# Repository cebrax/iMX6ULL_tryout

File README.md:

# iMX6ULL_tryout

This is a test board to get iMX6ULL up and running using KiCad 5.99

The board has:

- iMX6ULL 900MHz MCIMX6Y2DVM09AB
- 512MB DDR3L RAM
- An SD card slot
- 2 x USB connector
- An ethernet PHY and connector with magnetics
- A 40-pin LCD connector
- Various pinouts of GPIO, RS232 and such..

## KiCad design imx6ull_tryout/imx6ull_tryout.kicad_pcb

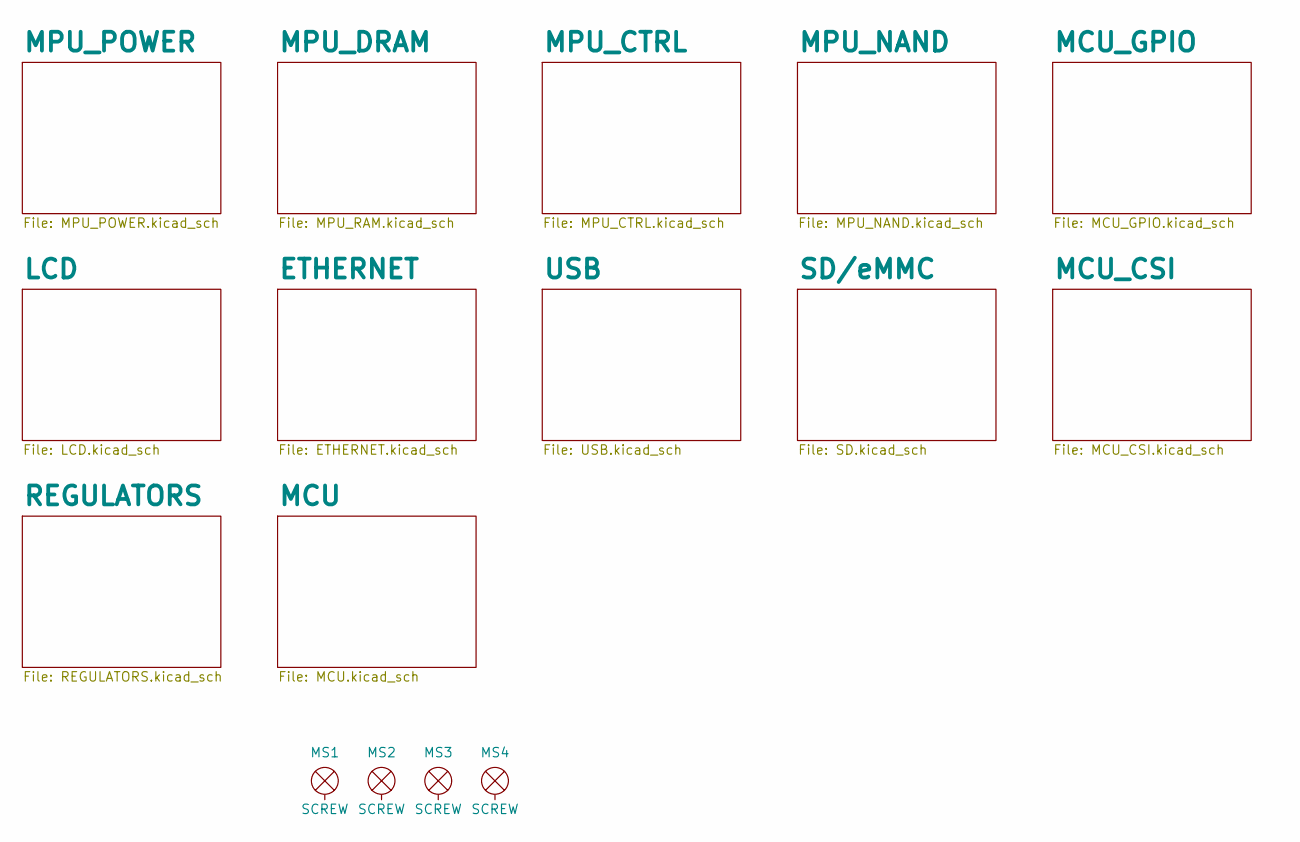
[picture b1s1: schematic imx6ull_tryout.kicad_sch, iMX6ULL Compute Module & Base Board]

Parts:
MS1, MS2, MS3, MS4: SCREW; M3-Screw-Front

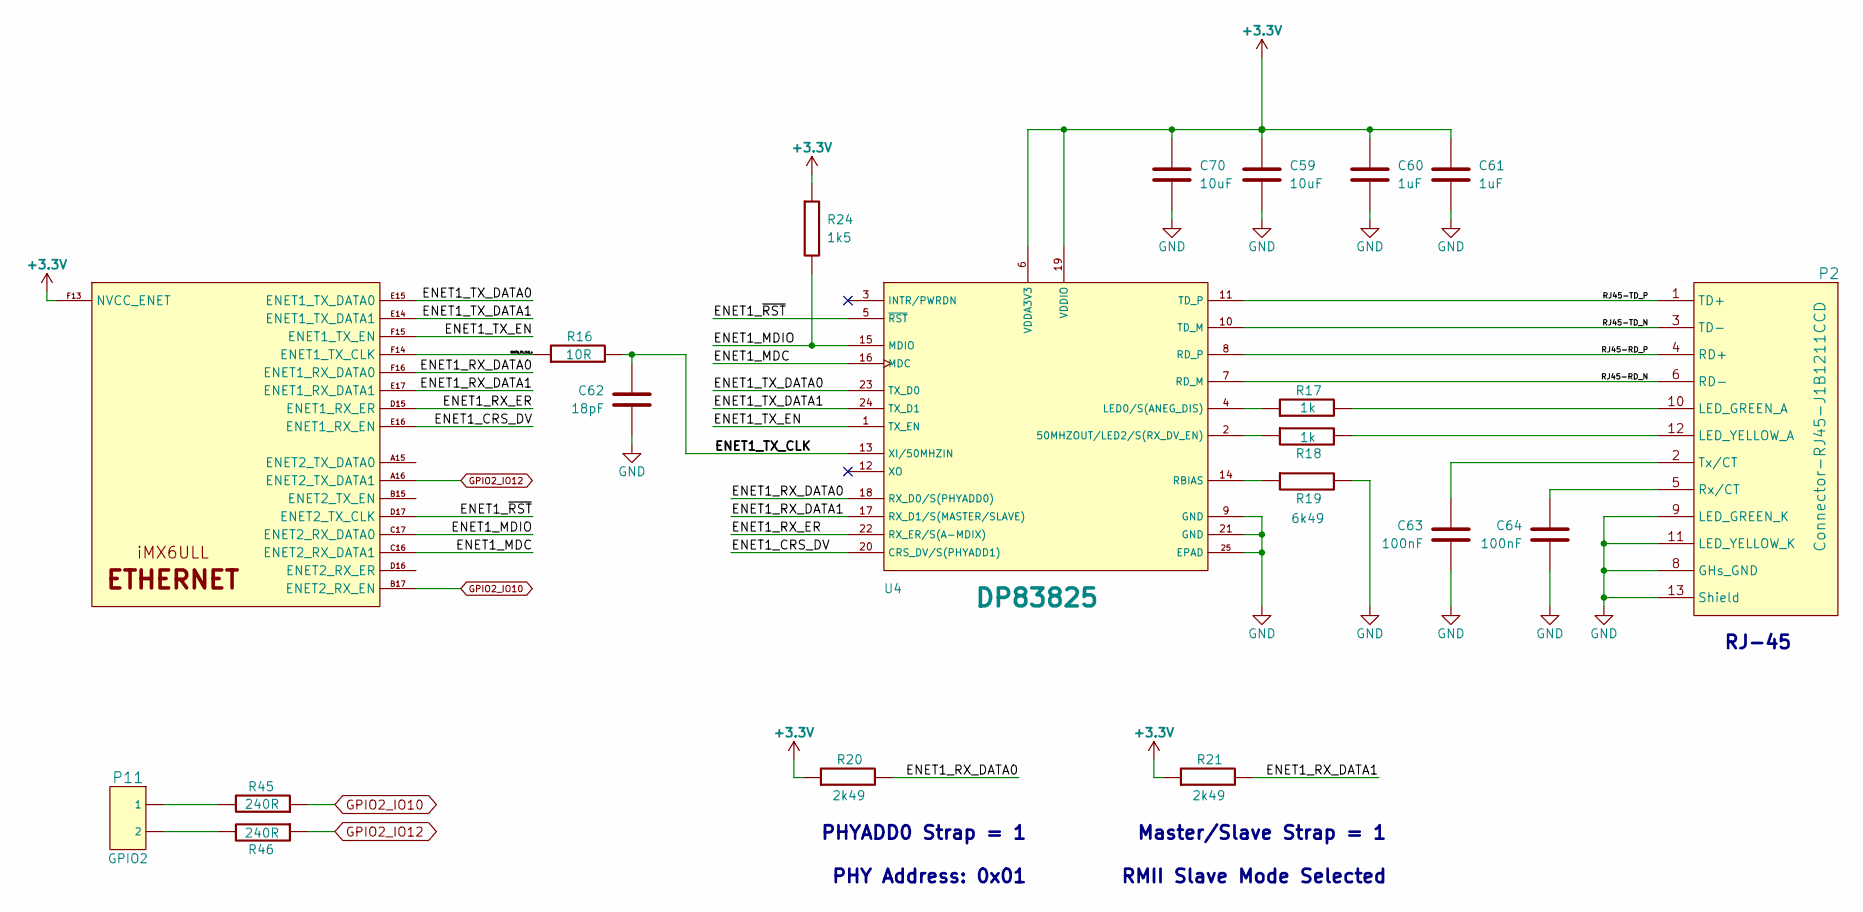
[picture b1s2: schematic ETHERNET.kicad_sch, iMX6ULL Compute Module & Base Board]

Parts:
C59, C70: 10uF; IPC-SMD-C-0402; Voltage 16V
C60, C61: 1uF; IPC-SMD-C-0402; Voltage 10V
C62: 18pF; IPC-SMD-C-0402; Voltage 50V
C63, C64: 100nF; IPC-SMD-C-0805; Voltage 50V
P2: Connector-RJ45-J1B1211CCD
P11: GPIO2; Connector-Male-Breakaway-2pins
R16: 10R; IPC-SMD-R-0402
R17, R18: 1k; IPC-SMD-R-0805
R19: 6k49; IPC-SMD-R-0603
R20, R21: 2k49; IPC-SMD-R-0603
R24: 1k5; IPC-SMD-R-0603
R45, R46: 240R; IPC-SMD-R-0402
U1: iMX6ULL; BGA289C80P17X17_1400X1400X132N
U4: DP83825; IPC-WQFN-24

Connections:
+3V3: C59.1, C60.1, C61.1, C70.1, R20.1, R21.1, R24.1, U1.F13 (NVCC_ENET), U4.6 (VDDA3V3), U4.19 (VDDIO); also elsewhere on the board
/ETHERNET/ENET1_CRS_DV: U1.E16 (ENET1_RX_EN), U4.20 (CRS_DV/S(PHYADD1))
/ETHERNET/ENET1_MDC: U1.C16 (ENET2_RX_DATA1), U4.16 (MDC)
/ETHERNET/ENET1_MDIO: R24.2, U1.C17 (ENET2_RX_DATA0), U4.15 (MDIO)
/ETHERNET/ENET1_RX_DATA0: R20.2, U1.F16 (ENET1_RX_DATA0), U4.18 (RX_D0/S(PHYADD0))
/ETHERNET/ENET1_RX_DATA1: R21.2, U1.E17 (ENET1_RX_DATA1), U4.17 (RX_D1/S(MASTER/SLAVE))
/ETHERNET/ENET1_RX_ER: U1.D15 (ENET1_RX_ER), U4.22 (RX_ER/S(A-MDIX))
/ETHERNET/ENET1_TX_CLK: C62.1, R16.2, U4.13 (XI/50MHZIN)
/ETHERNET/ENET1_TX_CLK_s: R16.1, U1.F14 (ENET1_TX_CLK)
/ETHERNET/ENET1_TX_DATA0: U1.E15 (ENET1_TX_DATA0), U4.23 (TX_D0)
/ETHERNET/ENET1_TX_DATA1: U1.E14 (ENET1_TX_DATA1), U4.24 (TX_D1)
/ETHERNET/ENET1_TX_EN: U1.F15 (ENET1_TX_EN), U4.1 (TX_EN)
/ETHERNET/ENET1_~RST: U1.D17 (ENET2_TX_CLK), U4.5 (~RST)
/ETHERNET/RJ45-RD_N: P2.6 (RD-), U4.7 (RD_M)
/ETHERNET/RJ45-RD_P: P2.4 (RD+), U4.8 (RD_P)
/ETHERNET/RJ45-TD_N: P2.3 (TD-), U4.10 (TD_M)
/ETHERNET/RJ45-TD_P: P2.1 (TD+), U4.11 (TD_P)
GND: C59.2, C60.2, C61.2, C62.2, C63.2, C64.2, C70.2, P2.8 (GHs_GND), P2.9 (LED_GREEN_K), P2.11 (LED_YELLOW_K), P2.13 (Shield), R19.2, U4.9 (GND), U4.21 (GND), U4.25 (EPAD); also elsewhere on the board
GPIO2_IO10: R45.1, U1.B17 (ENET2_RX_EN)
GPIO2_IO12: R46.1, U1.A16 (ENET2_TX_DATA1)
unnamed: C63.1, P2.2 (Tx/CT)
unnamed: C64.1, P2.5 (Rx/CT)
unnamed: P2.10 (LED_GREEN_A), R17.2
unnamed: P2.12 (LED_YELLOW_A), R18.2
unnamed: P11.1, R45.2
unnamed: P11.2, R46.2
unnamed: R17.1, U4.4 (LED0/S(ANEG_DIS))
unnamed: R18.1, U4.2 (50MHZOUT/LED2/S(RX_DV_EN))
unnamed: R19.1, U4.14 (RBIAS)

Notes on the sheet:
PHYADD0 Strap = 1 PHY Address: 0x01
Master/Slave Strap = 1 RMII Slave Mode Selected
RJ-45

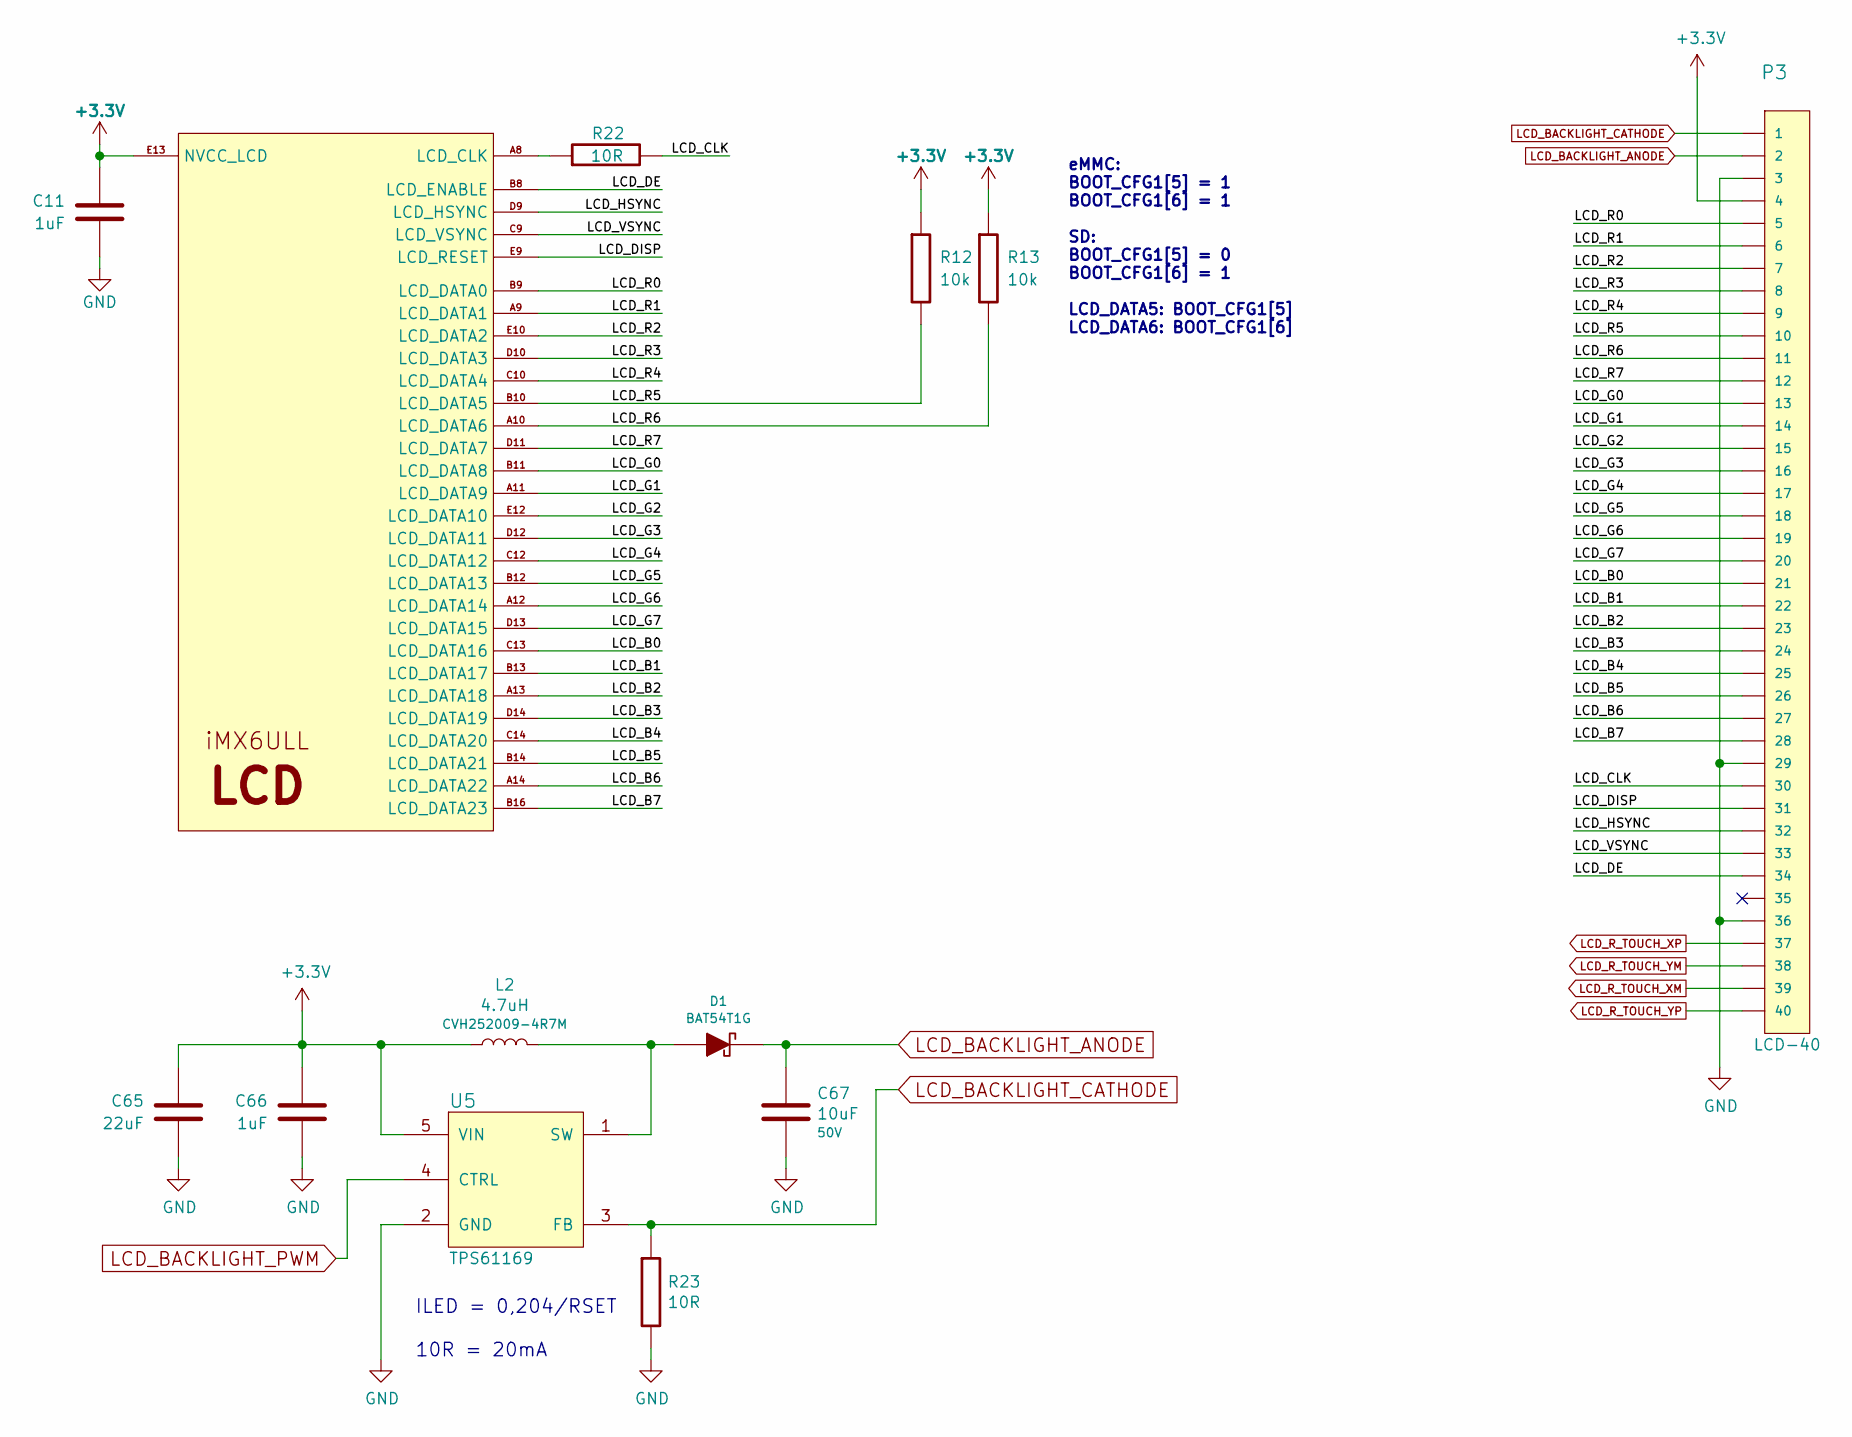
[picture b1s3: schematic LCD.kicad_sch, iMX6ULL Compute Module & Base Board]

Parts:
C11, C66: 1uF; IPC-SMD-C-0402; Voltage 10V
C65: 22uF; IPC-SMD-C-0603; Voltage 6.3V
C67: 10uF; IPC-SMD-C-1206; Voltage 50V
D1: BAT54T1G; IPC-SOD-123
L2: 4.7uH; IPC-SMD-R-0805; Part No CVH252009-4R7M
P3: LCD-40; Connector-SMD-ZIF-40-pin
R12, R13: 10k; IPC-SMD-R-0603
R22: 10R; IPC-SMD-R-0402
R23: 10R; IPC-SMD-R-0805
U1: iMX6ULL; BGA289C80P17X17_1400X1400X132N
U5: TPS61169; IPC-SC-70-5

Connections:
+3V3: C11.1, C65.1, C66.1, L2.2, P3.4, R12.1, R13.1, U1.E13 (NVCC_LCD), U5.5 (VIN); also elsewhere on the board
/LCD/LCD_B0: P3.21, U1.C13 (LCD_DATA16)
/LCD/LCD_B1: P3.22, U1.B13 (LCD_DATA17)
/LCD/LCD_B2: P3.23, U1.A13 (LCD_DATA18)
/LCD/LCD_B3: P3.24, U1.D14 (LCD_DATA19)
/LCD/LCD_B4: P3.25, U1.C14 (LCD_DATA20)
/LCD/LCD_B5: P3.26, U1.B14 (LCD_DATA21)
/LCD/LCD_B6: P3.27, U1.A14 (LCD_DATA22)
/LCD/LCD_B7: P3.28, U1.B16 (LCD_DATA23)
/LCD/LCD_CLK: P3.30, R22.2
/LCD/LCD_DE: P3.34, U1.B8 (LCD_ENABLE)
/LCD/LCD_DISP: P3.31, U1.E9 (LCD_RESET)
/LCD/LCD_G0: P3.13, U1.B11 (LCD_DATA8)
/LCD/LCD_G1: P3.14, U1.A11 (LCD_DATA9)
/LCD/LCD_G2: P3.15, U1.E12 (LCD_DATA10)
/LCD/LCD_G3: P3.16, U1.D12 (LCD_DATA11)
/LCD/LCD_G4: P3.17, U1.C12 (LCD_DATA12)
/LCD/LCD_G5: P3.18, U1.B12 (LCD_DATA13)
/LCD/LCD_G6: P3.19, U1.A12 (LCD_DATA14)
/LCD/LCD_G7: P3.20, U1.D13 (LCD_DATA15)
/LCD/LCD_HSYNC: P3.32, U1.D9 (LCD_HSYNC)
/LCD/LCD_R0: P3.5, U1.B9 (LCD_DATA0)
/LCD/LCD_R1: P3.6, U1.A9 (LCD_DATA1)
/LCD/LCD_R2: P3.7, U1.E10 (LCD_DATA2)
/LCD/LCD_R3: P3.8, U1.D10 (LCD_DATA3)
/LCD/LCD_R4: P3.9, U1.C10 (LCD_DATA4)
/LCD/LCD_R5: P3.10, R12.2, U1.B10 (LCD_DATA5)
/LCD/LCD_R6: P3.11, R13.2, U1.A10 (LCD_DATA6)
/LCD/LCD_R7: P3.12, U1.D11 (LCD_DATA7)
/LCD/LCD_VSYNC: P3.33, U1.C9 (LCD_VSYNC)
GND: C11.2, C65.2, C66.2, C67.2, P3.3, P3.29, P3.36, R23.2, U5.2 (GND); also elsewhere on the board
LCD_BACKLIGHT_ANODE: C67.1, D1.2 (K), P3.2
LCD_BACKLIGHT_CATHODE: P3.1, R23.1, U5.3 (FB)
LCD_BACKLIGHT_PWM: U5.4 (CTRL); also elsewhere on the board
LCD_R_TOUCH_XM: P3.39; also elsewhere on the board
LCD_R_TOUCH_XP: P3.37; also elsewhere on the board
LCD_R_TOUCH_YM: P3.38; also elsewhere on the board
LCD_R_TOUCH_YP: P3.40; also elsewhere on the board
unnamed: D1.1 (A), L2.1, U5.1 (SW)
unnamed: R22.1, U1.A8 (LCD_CLK)

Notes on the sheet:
ILED = 0,204/RSET 10R = 20mA
eMMC: BOOT_CFG1[5] = 1 BOOT_CFG1[6] = 1 SD: BOOT_CFG1[5] = 0 BOOT_CFG1[6] = 1 LCD_DATA5: BOOT_CFG1[5] LCD_DATA6: BOOT_CFG1[6]

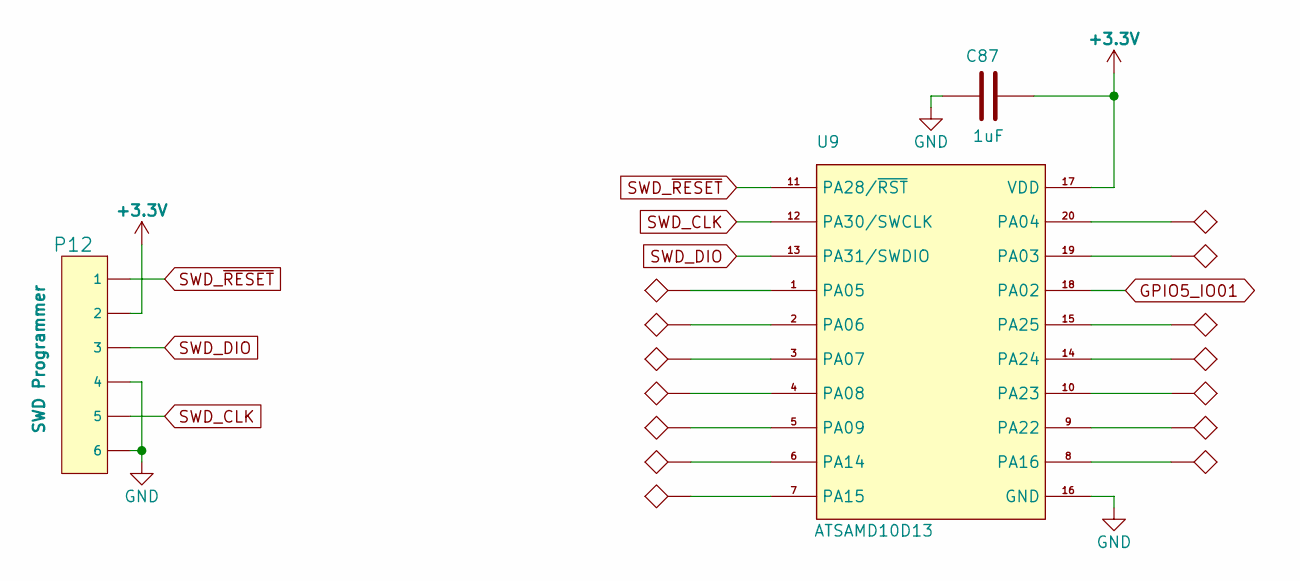
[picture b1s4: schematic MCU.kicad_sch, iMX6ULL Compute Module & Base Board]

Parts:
C87: 1uF; IPC-SMD-C-0402
P12: SWD Programmer; TC2030-IDC-NL-FP-6-pin
TP1, TP2, TP3, TP4, TP5, TP6, TP7, TP8, TP9, TP10, TP11, TP12, TP13, TP14: TEST_POINT; TP-40th-Without-Silkscreen
U9: ATSAMD10D13; IPC-SOIC-20

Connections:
+3V3: C87.1, P12.2, U9.17 (VDD); also elsewhere on the board
GND: C87.2, P12.4, P12.6, U9.16 (GND); also elsewhere on the board
GPIO5_IO01: U9.18 (PA02); also elsewhere on the board
unnamed: TP9.1, U9.3 (PA07)
unnamed: TP10.1, U9.10 (PA23)
unnamed: TP11.1, U9.4 (PA08)
unnamed: TP13.1, U9.1 (PA05)
unnamed: TP14.1, U9.2 (PA06)
unnamed: TP2.1, U9.5 (PA09)
unnamed: TP4.1, U9.6 (PA14)
unnamed: TP6.1, U9.7 (PA15)
unnamed: TP7.1, U9.8 (PA16)
unnamed: TP8.1, U9.9 (PA22)
unnamed: TP5.1, U9.14 (PA24)
unnamed: TP3.1, U9.15 (PA25)
unnamed: TP12.1, U9.19 (PA03)
unnamed: TP1.1, U9.20 (PA04)
SWD_CLK: P12.5, U9.12 (PA30/SWCLK)
SWD_DIO: P12.3, U9.13 (PA31/SWDIO)
SWD_~RESET: P12.1, U9.11 (PA28/~RST)

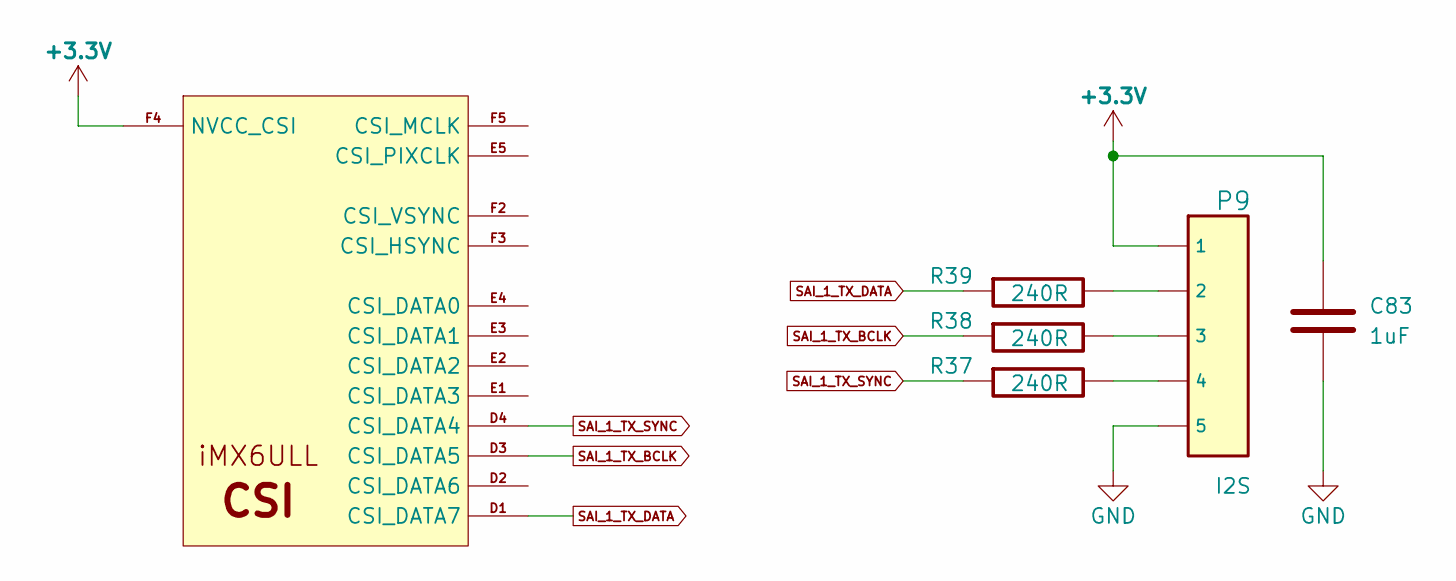
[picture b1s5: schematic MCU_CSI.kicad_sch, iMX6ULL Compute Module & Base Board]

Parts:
C83: 1uF; IPC-SMD-C-0402; Voltage 10V
P9: I2S; Connector-Male-Breakaway-5pins
R37, R38, R39: 240R; IPC-SMD-R-0402
U1: iMX6ULL; BGA289C80P17X17_1400X1400X132N

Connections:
+3V3: C83.1, P9.1, U1.F4 (NVCC_CSI); also elsewhere on the board
GND: C83.2, P9.5; also elsewhere on the board
unnamed: P9.2, R39.2
unnamed: P9.3, R38.2
unnamed: P9.4, R37.2
SAI_1_TX_BCLK: R38.1, U1.D3 (CSI_DATA5)
SAI_1_TX_DATA: R39.1, U1.D1 (CSI_DATA7)
SAI_1_TX_SYNC: R37.1, U1.D4 (CSI_DATA4)

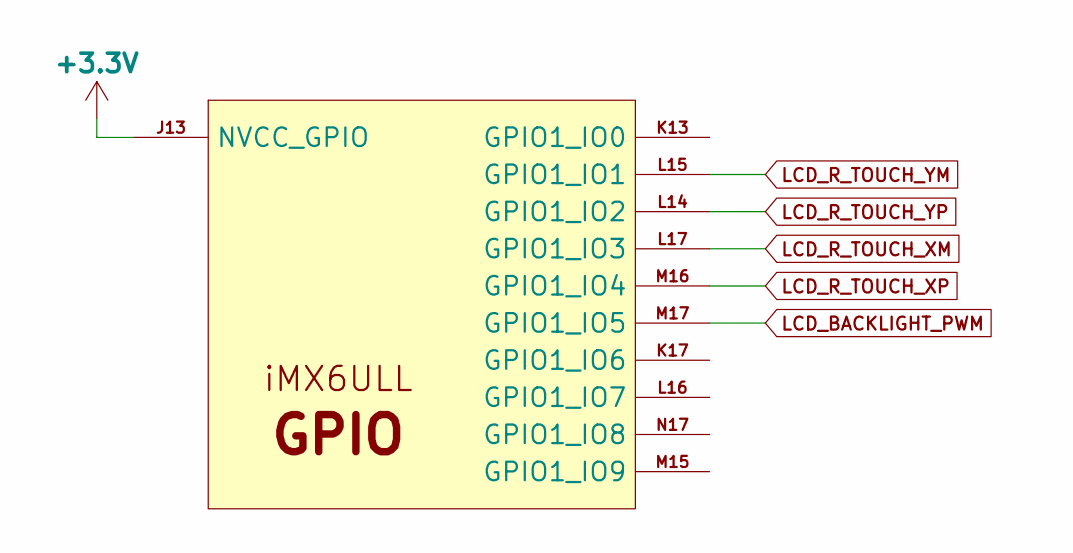
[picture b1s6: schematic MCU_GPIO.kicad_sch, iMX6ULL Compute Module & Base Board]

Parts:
U1: iMX6ULL; BGA289C80P17X17_1400X1400X132N

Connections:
+3V3: U1.J13 (NVCC_GPIO); also elsewhere on the board
LCD_BACKLIGHT_PWM: U1.M17 (GPIO1_IO5); also elsewhere on the board
LCD_R_TOUCH_XM: U1.L17 (GPIO1_IO3); also elsewhere on the board
LCD_R_TOUCH_XP: U1.M16 (GPIO1_IO4); also elsewhere on the board
LCD_R_TOUCH_YM: U1.L15 (GPIO1_IO1); also elsewhere on the board
LCD_R_TOUCH_YP: U1.L14 (GPIO1_IO2); also elsewhere on the board

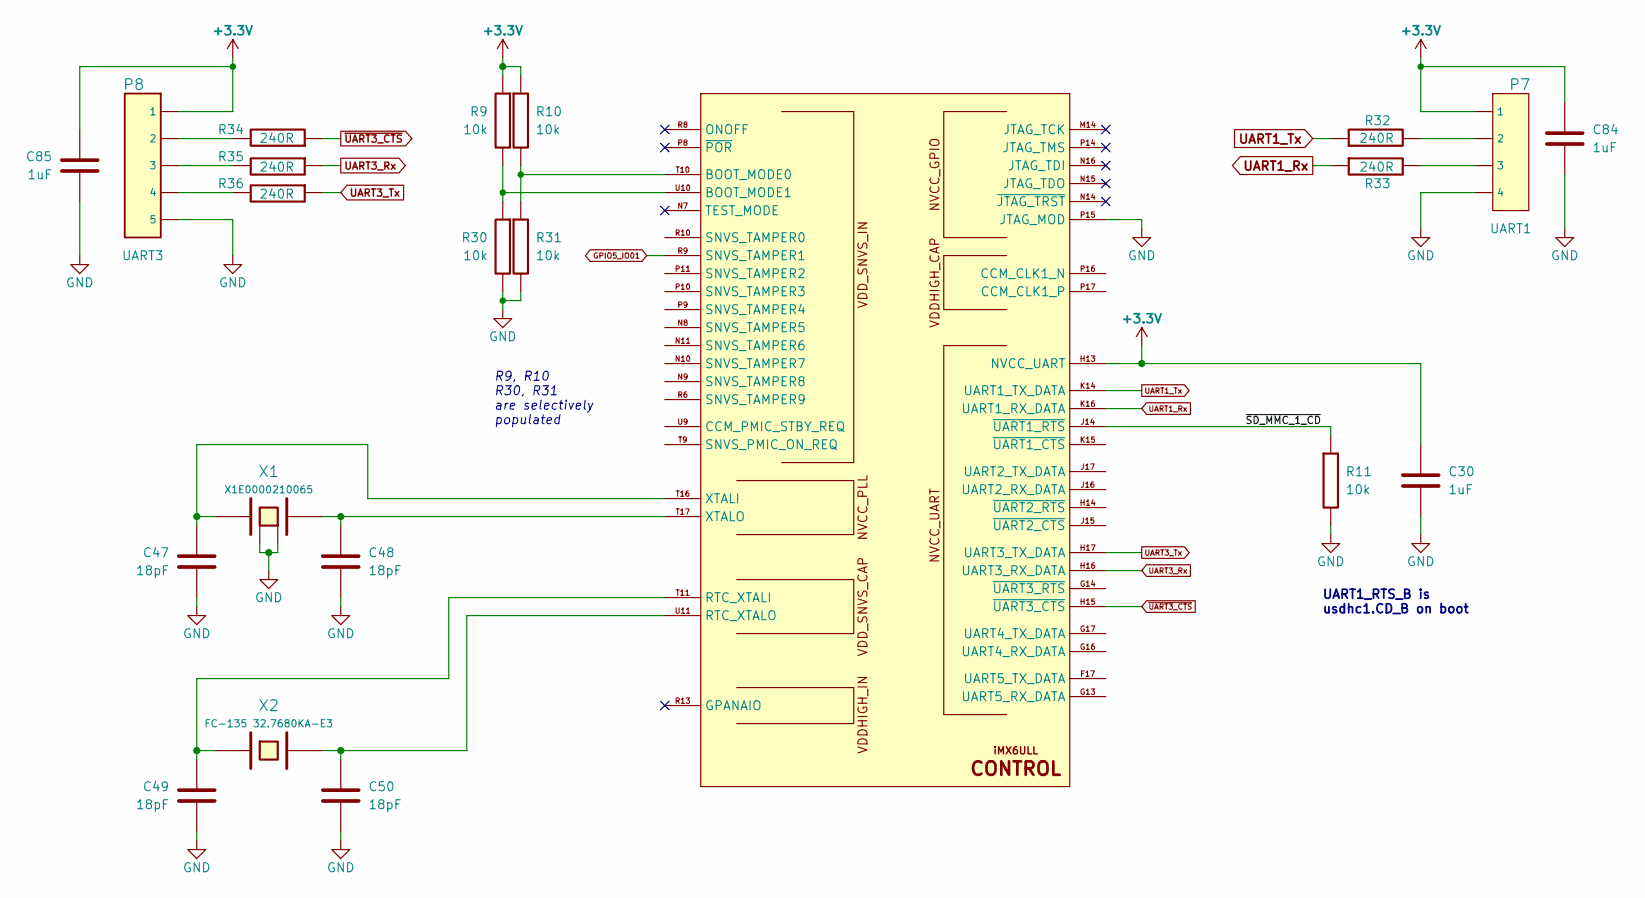
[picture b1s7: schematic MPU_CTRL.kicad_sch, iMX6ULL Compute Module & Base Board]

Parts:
C30, C84, C85: 1uF; IPC-SMD-C-0402; Voltage 10V
C47, C48, C49, C50: 18pF; IPC-SMD-C-0402; Voltage 50V
P7: UART1; Connector-Male-Breakaway-4pins
P8: UART3; Connector-Male-Breakaway-5pins
R9, R10, R11, R30, R31: 10k; IPC-SMD-R-0402
R32, R33, R34, R35, R36: 240R; IPC-SMD-R-0402
U1: iMX6ULL; BGA289C80P17X17_1400X1400X132N
X1: X1E0000210065; XTAL-SMD-3.2mm-2.5mm
X2: FC-135 32.7680KA-E3; CRYSTAL-EPSON-FC-135

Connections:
+3V3: C30.1, C84.1, C85.1, P7.1, P8.1, R9.1, R10.1, U1.H13 (NVCC_UART); also elsewhere on the board
/MPU_CTRL/~SD_MMC_1_CD: R11.1, U1.J14 (~UART1_RTS~)
GND: C30.2, C47.2, C48.2, C49.2, C50.2, C84.2, C85.2, P7.4, P8.5, R11.2, R30.2, R31.2, U1.P15 (JTAG_MOD), X1.2 (Case), X1.4 (Case); also elsewhere on the board
GPIO5_IO01: U1.R9 (SNVS_TAMPER1); also elsewhere on the board
unnamed: C47.1, U1.T16 (XTALI), X1.3
unnamed: C48.1, U1.T17 (XTALO), X1.1
unnamed: C49.1, U1.T11 (RTC_XTALI), X2.1
unnamed: C50.1, U1.U11 (RTC_XTALO), X2.2
unnamed: P7.2, R32.2
unnamed: P7.3, R33.2
unnamed: P8.2, R34.2
unnamed: P8.3, R35.2
unnamed: P8.4, R36.2
unnamed: R10.2, R31.1, U1.T10 (BOOT_MODE0)
unnamed: R9.2, R30.1, U1.U10 (BOOT_MODE1)
UART1_Rx: R33.1, U1.K16 (UART1_RX_DATA)
UART1_Tx: R32.1, U1.K14 (UART1_TX_DATA)
UART3_Rx: R35.1, U1.H16 (UART3_RX_DATA)
UART3_Tx: R36.1, U1.H17 (UART3_TX_DATA)
~UART3_CTS: R34.1, U1.H15 (~UART3_CTS~)

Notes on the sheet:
R9, R10 R30, R31 are selectively populated
UART1_RTS_B is usdhc1.CD_B on boot

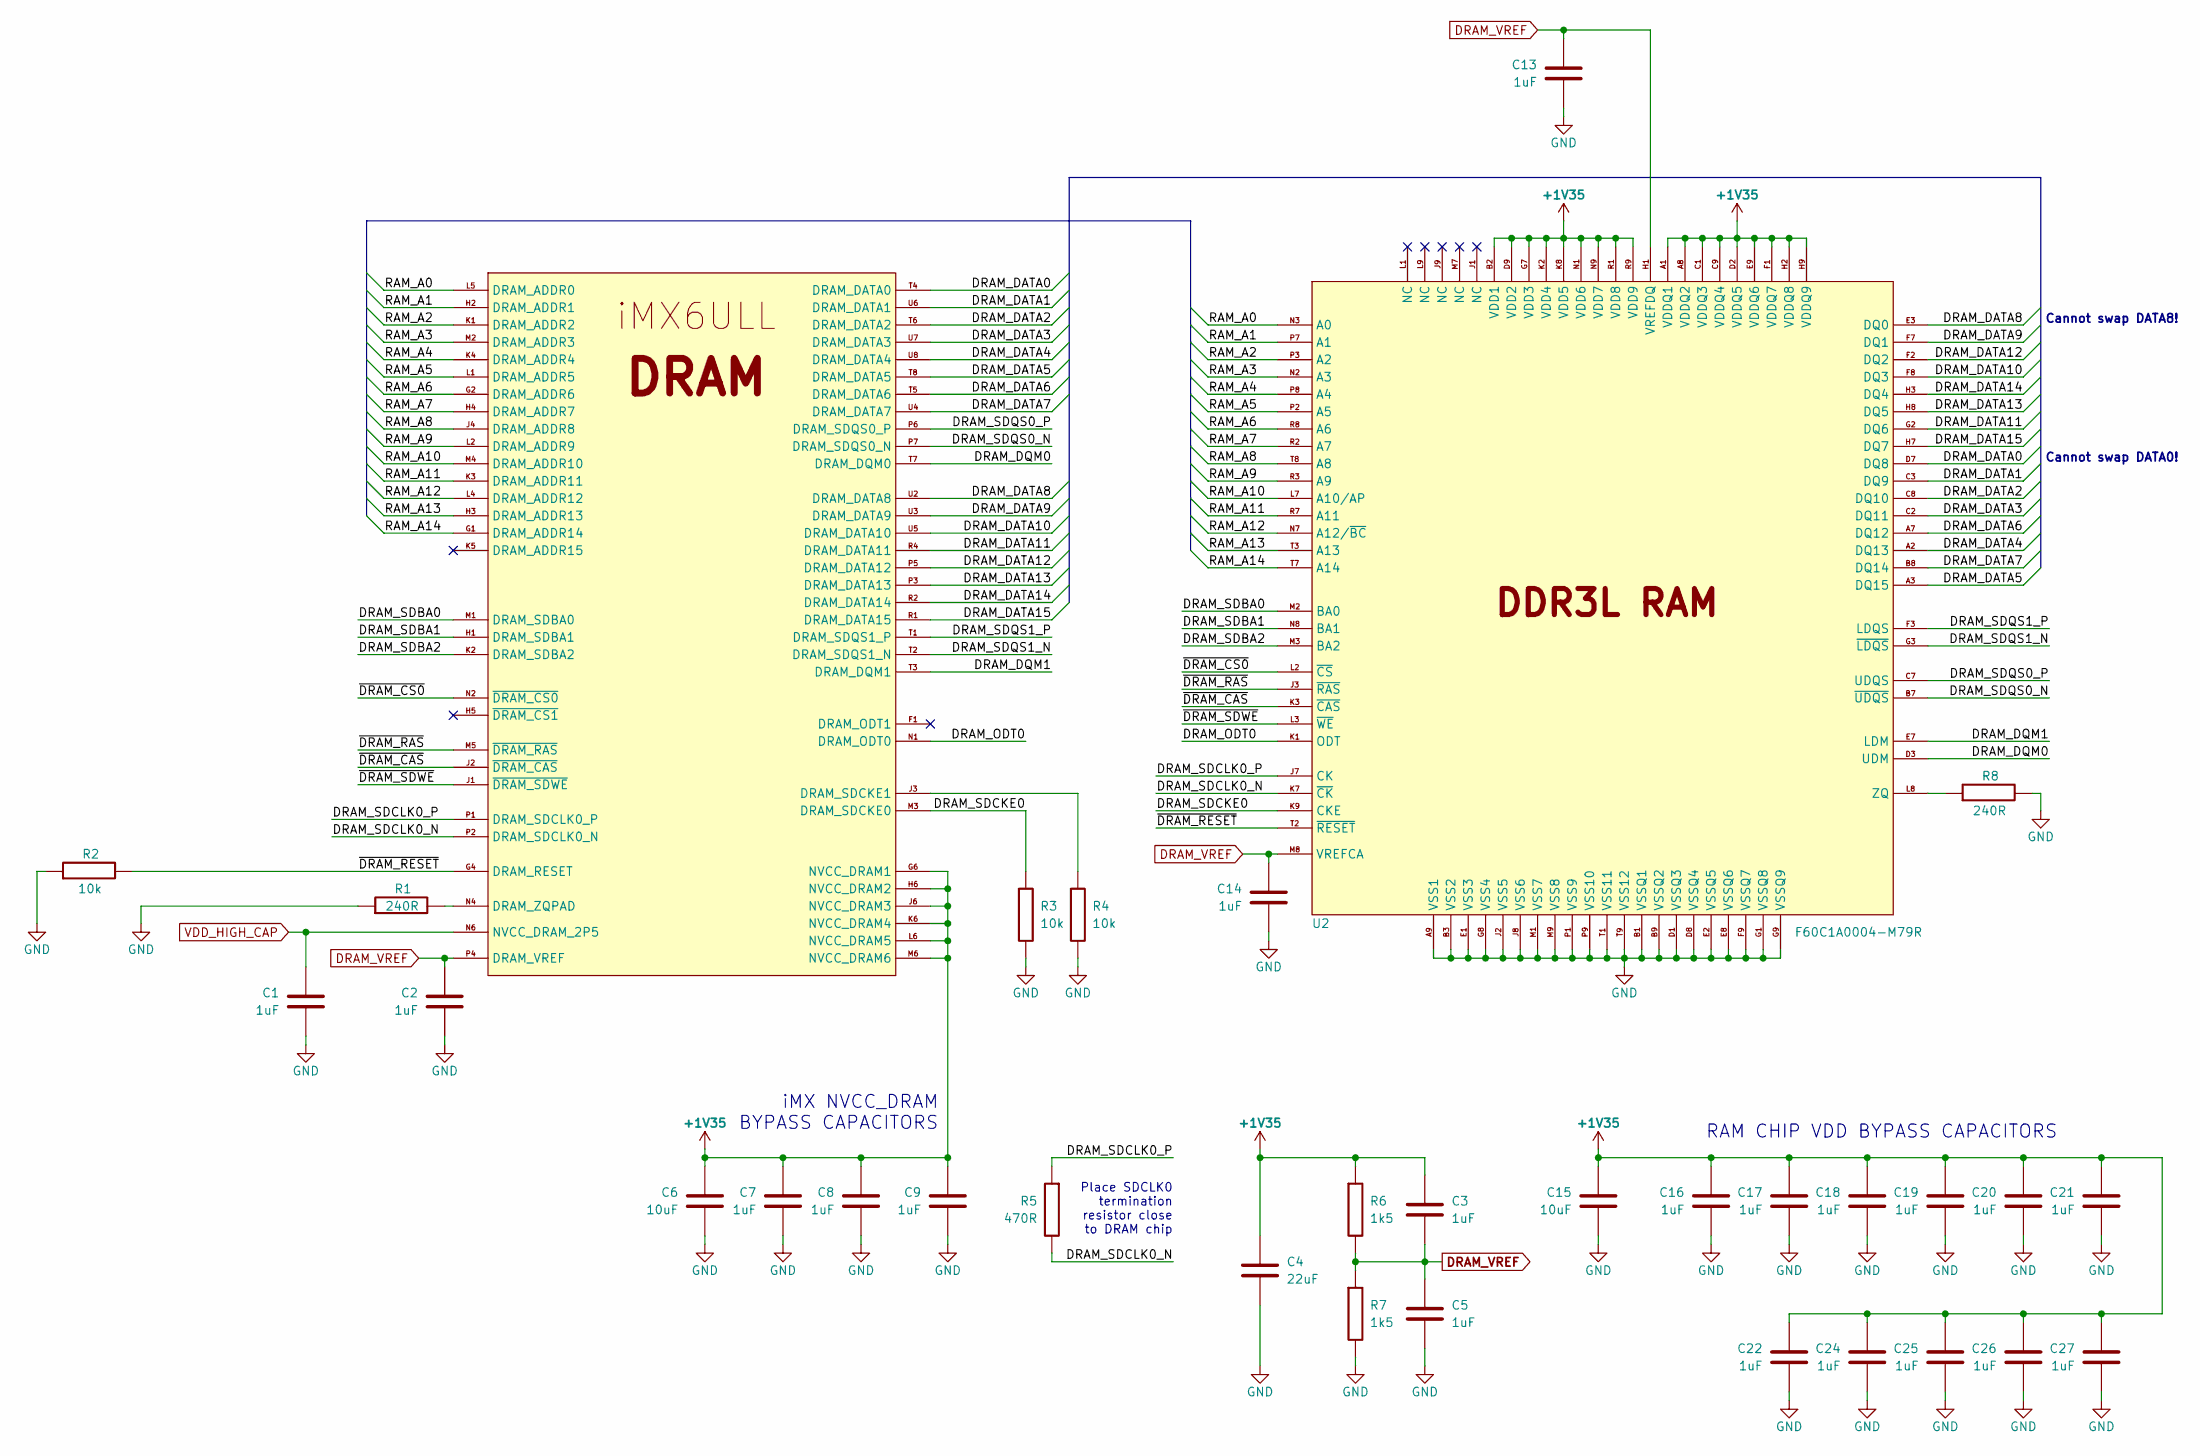
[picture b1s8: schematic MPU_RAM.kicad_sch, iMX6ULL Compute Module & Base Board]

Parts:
C1, C2, C7, C8, C9, C13, C14, C16, C17, C18, C19, C20, C21, C22, C24, C25, C26, C27: 1uF; IPC-SMD-C-0402; Voltage 10V
C3, C5: 1uF; IPC-SMD-C-0603; Voltage 16V
C4: 22uF; IPC-SMD-C-0603; Voltage 6.3V
C6: 10uF; IPC-SMD-C-0402; Voltage 16V
C15: 10uF; IPC-SMD-C-0805; Voltage 16V
R1, R8: 240R; IPC-SMD-R-0402
R2, R3, R4: 10k; IPC-SMD-R-0402
R5: 470R; IPC-SMD-R-0402
R6, R7: 1k5; IPC-SMD-R-0603
U1: iMX6ULL; BGA289C80P17X17_1400X1400X132N
U2: F60C1A0004-M79R; BGA96C80P9X16_1400X800X120

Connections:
+1V35: C3.1, C4.1, C6.1, C7.1, C8.1, C9.1, C15.1, C16.1, C17.1, C18.1, C19.1, C20.1, C21.1, C22.1, C24.1, C25.1, C26.1, C27.1, R6.1, U1.G6 (NVCC_DRAM1), U1.H6 (NVCC_DRAM2), U1.J6 (NVCC_DRAM3), U1.K6 (NVCC_DRAM4), U1.L6 (NVCC_DRAM5), U1.M6 (NVCC_DRAM6), U2.A1 (VDDQ1), U2.A8 (VDDQ2), U2.B2 (VDD1), U2.C1 (VDDQ3), U2.C9 (VDDQ4), U2.D2 (VDDQ5), U2.D9 (VDD2), U2.E9 (VDDQ6), U2.F1 (VDDQ7), U2.G7 (VDD3), U2.H2 (VDDQ8), U2.H9 (VDDQ9), U2.K2 (VDD4), U2.K8 (VDD5), U2.N1 (VDD6), U2.N9 (VDD7), U2.R1 (VDD8), U2.R9 (VDD9); also elsewhere on the board
/MPU_DRAM/DRAM_DATA0: U1.T4 (DRAM_DATA0), U2.D7 (DQ8)
/MPU_DRAM/DRAM_DATA1: U1.U6 (DRAM_DATA1), U2.C3 (DQ9)
/MPU_DRAM/DRAM_DATA2: U1.T6 (DRAM_DATA2), U2.C8 (DQ10)
/MPU_DRAM/DRAM_DATA3: U1.U7 (DRAM_DATA3), U2.C2 (DQ11)
/MPU_DRAM/DRAM_DATA4: U1.U8 (DRAM_DATA4), U2.A2 (DQ13)
/MPU_DRAM/DRAM_DATA5: U1.T8 (DRAM_DATA5), U2.A3 (DQ15)
/MPU_DRAM/DRAM_DATA6: U1.T5 (DRAM_DATA6), U2.A7 (DQ12)
/MPU_DRAM/DRAM_DATA7: U1.U4 (DRAM_DATA7), U2.B8 (DQ14)
/MPU_DRAM/DRAM_DATA8: U1.U2 (DRAM_DATA8), U2.E3 (DQ0)
/MPU_DRAM/DRAM_DATA9: U1.U3 (DRAM_DATA9), U2.F7 (DQ1)
/MPU_DRAM/DRAM_DATA10: U1.U5 (DRAM_DATA10), U2.F8 (DQ3)
/MPU_DRAM/DRAM_DATA11: U1.R4 (DRAM_DATA11), U2.G2 (DQ6)
/MPU_DRAM/DRAM_DATA12: U1.P5 (DRAM_DATA12), U2.F2 (DQ2)
/MPU_DRAM/DRAM_DATA13: U1.P3 (DRAM_DATA13), U2.H8 (DQ5)
/MPU_DRAM/DRAM_DATA14: U1.R2 (DRAM_DATA14), U2.H3 (DQ4)
/MPU_DRAM/DRAM_DATA15: U1.R1 (DRAM_DATA15), U2.H7 (DQ7)
/MPU_DRAM/DRAM_DQM0: U1.T7 (DRAM_DQM0), U2.D3 (UDM)
/MPU_DRAM/DRAM_DQM1: U1.T3 (DRAM_DQM1), U2.E7 (LDM)
/MPU_DRAM/DRAM_ODT0: U1.N1 (DRAM_ODT0), U2.K1 (ODT)
/MPU_DRAM/DRAM_SDBA0: U1.M1 (DRAM_SDBA0), U2.M2 (BA0)
/MPU_DRAM/DRAM_SDBA1: U1.H1 (DRAM_SDBA1), U2.N8 (BA1)
/MPU_DRAM/DRAM_SDBA2: U1.K2 (DRAM_SDBA2), U2.M3 (BA2)
/MPU_DRAM/DRAM_SDCKE0: R3.1, U1.M3 (DRAM_SDCKE0), U2.K9 (CKE)
/MPU_DRAM/DRAM_SDCLK0_N: R5.2, U1.P2 (DRAM_SDCLK0_N), U2.K7 (~CK~)
/MPU_DRAM/DRAM_SDCLK0_P: R5.1, U1.P1 (DRAM_SDCLK0_P), U2.J7 (CK)
/MPU_DRAM/DRAM_SDQS0_N: U1.P7 (DRAM_SDQS0_N), U2.B7 (~UDQS~)
/MPU_DRAM/DRAM_SDQS0_P: U1.P6 (DRAM_SDQS0_P), U2.C7 (UDQS)
/MPU_DRAM/DRAM_SDQS1_N: U1.T2 (DRAM_SDQS1_N), U2.G3 (~LDQS~)
/MPU_DRAM/DRAM_SDQS1_P: U1.T1 (DRAM_SDQS1_P), U2.F3 (LDQS)
/MPU_DRAM/RAM_A0: U1.L5 (DRAM_ADDR0), U2.N3 (A0)
/MPU_DRAM/RAM_A1: U1.H2 (DRAM_ADDR1), U2.P7 (A1)
/MPU_DRAM/RAM_A2: U1.K1 (DRAM_ADDR2), U2.P3 (A2)
/MPU_DRAM/RAM_A3: U1.M2 (DRAM_ADDR3), U2.N2 (A3)
/MPU_DRAM/RAM_A4: U1.K4 (DRAM_ADDR4), U2.P8 (A4)
/MPU_DRAM/RAM_A5: U1.L1 (DRAM_ADDR5), U2.P2 (A5)
/MPU_DRAM/RAM_A6: U1.G2 (DRAM_ADDR6), U2.R8 (A6)
/MPU_DRAM/RAM_A7: U1.H4 (DRAM_ADDR7), U2.R2 (A7)
/MPU_DRAM/RAM_A8: U1.J4 (DRAM_ADDR8), U2.T8 (A8)
/MPU_DRAM/RAM_A9: U1.L2 (DRAM_ADDR9), U2.R3 (A9)
/MPU_DRAM/RAM_A10: U1.M4 (DRAM_ADDR10), U2.L7 (A10/AP)
/MPU_DRAM/RAM_A11: U1.K3 (DRAM_ADDR11), U2.R7 (A11)
/MPU_DRAM/RAM_A12: U1.L4 (DRAM_ADDR12), U2.N7 (A12/~BC~)
/MPU_DRAM/RAM_A13: U1.H3 (DRAM_ADDR13), U2.T3 (A13)
/MPU_DRAM/RAM_A14: U1.G1 (DRAM_ADDR14), U2.T7 (A14)
/MPU_DRAM/~DRAM_CAS: U1.J2 (~DRAM_CAS~), U2.K3 (~CAS~)
/MPU_DRAM/~DRAM_CS0: U1.N2 (~DRAM_CS0~), U2.L2 (~CS~)
/MPU_DRAM/~DRAM_RAS: U1.M5 (~DRAM_RAS~), U2.J3 (~RAS~)
/MPU_DRAM/~DRAM_RESET: R2.2, U1.G4 (DRAM_RESET), U2.T2 (~RESET~)
/MPU_DRAM/~DRAM_SDWE: U1.J1 (~DRAM_SDWE~), U2.L3 (~WE~)
DRAM_VREF: C2.1, C3.2, C5.1, C13.1, C14.1, R6.2, R7.1, U1.P4 (DRAM_VREF), U2.H1 (VREFDQ), U2.M8 (VREFCA)
GND: C1.2, C2.2, C4.2, C5.2, C6.2, C7.2, C8.2, C9.2, C13.2, C14.2, C15.2, C16.2, C17.2, C18.2, C19.2, C20.2, C21.2, C22.2, C24.2, C25.2, C26.2, C27.2, R1.1, R2.1, R3.2, R4.2, R7.2, R8.2, U2.A9 (VSS1), U2.B1 (VSSQ1), U2.B3 (VSS2), U2.B9 (VSSQ2), U2.D1 (VSSQ3), U2.D8 (VSSQ4), U2.E1 (VSS3), U2.E2 (VSSQ5), U2.E8 (VSSQ6), U2.F9 (VSSQ7), U2.G1 (VSSQ8), U2.G8 (VSS4), U2.G9 (VSSQ9), U2.J2 (VSS5), U2.J8 (VSS6), U2.M1 (VSS7), U2.M9 (VSS8), U2.P1 (VSS9), U2.P9 (VSS10), U2.T1 (VSS11), U2.T9 (VSS12); also elsewhere on the board
unnamed: R1.2, U1.N4 (DRAM_ZQPAD)
unnamed: R4.1, U1.J3 (DRAM_SDCKE1)
unnamed: R8.1, U2.L8 (ZQ)
VDD_HIGH_CAP: C1.1, U1.N6 (NVCC_DRAM_2P5); also elsewhere on the board

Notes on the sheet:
iMX NVCC_DRAM BYPASS CAPACITORS
Place SDCLK0 termination resistor close to DRAM chip
RAM CHIP VDD BYPASS CAPACITORS
Cannot swap DATA8!
Cannot swap DATA0!

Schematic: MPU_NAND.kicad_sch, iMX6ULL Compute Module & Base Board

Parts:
C10, C86: 1uF; IPC-SMD-C-0402; Voltage 10V
D3: LED; IPC-SMD-LED-0805
P10: ECSPI4; Connector-Male-Breakaway-7pins
R40, R41, R42, R43, R44: 240R; IPC-SMD-R-0402
R47: 1k5; IPC-SMD-R-0603
U1: iMX6ULL; BGA289C80P17X17_1400X1400X132N

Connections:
ECSPI4_MISO: R43.2, U1.A6 (NAND_DATA6)
ECSPI4_MOSI: R41.2, U1.B6 (NAND_DATA5)
ECSPI4_SCLK: R40.2, U1.C6 (NAND_DATA4)
ECSPI4_SS0: R42.2, U1.A5 (NAND_DATA7)
ECSPI4_SS1: R44.2, U1.B7 (NAND_DATA1)
+3V3: C10.1, C86.1, P10.1, U1.E7 (NVCC_NAND); also elsewhere on the board
GND: C10.2, C86.2, D3.2 (K), P10.7; also elsewhere on the board
unnamed: D3.1 (A), R47.2
unnamed: P10.2, R40.1
unnamed: P10.3, R41.1
unnamed: P10.4, R42.1
unnamed: P10.5, R43.1
unnamed: P10.6, R44.1
unnamed: R47.1, U1.A7 (NAND_DATA2)
SD1_DATA4: U1.A3 (~NAND_READY~)
SD1_DATA5: U1.C5 (~NAND_CE0~)
SD1_DATA6: U1.B5 (~NAND_CE1~)
SD1_DATA7: U1.A4 (NAND_CLE)

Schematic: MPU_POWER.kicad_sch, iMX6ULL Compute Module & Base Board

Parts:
C29, C31, C32, C33, C34, C36, C37, C38, C42, C43, C45: 1uF; IPC-SMD-C-0402; Voltage 10V
C35, C39, C40: 22uF; IPC-SMD-C-0603; Voltage 6.3V
C41, C44, C46: 10uF; IPC-SMD-C-0402; Voltage 16V
U1: iMX6ULL; BGA289C80P17X17_1400X1400X132N

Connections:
+1V35: C29.1, C40.1, U1.H9 (VDD_SOC_IN1), U1.H10 (VDD_SOC_IN2), U1.J9 (VDD_SOC_IN3), U1.J10 (VDD_SOC_IN4), U1.K9 (VDD_SOC_IN5), U1.K10 (VDD_SOC_IN6); also elsewhere on the board
+3V3: C31.1, C32.1, C41.1, U1.L13 (VDDA_ADC_3P3), U1.M13 (ADC_VREFH), U1.N13 (VDD_HIGH_IN), U1.P12 (VDD_SNVS_IN); also elsewhere on the board
/MPU_POWER/NVCC_PLL: C43.1, C44.1, U1.P13 (NVCC_PLL)
/MPU_POWER/VDD_ARM_CAP: C33.1, C34.1, C35.1, U1.G9 (VDD_ARM_CAP_1), U1.G10 (VDD_ARM_CAP_2), U1.G11 (VDD_ARM_CAP_3), U1.H11 (VDD_ARM_CAP_4)
/MPU_POWER/VDD_SNVS_CAP: C42.1, U1.N12 (VDD_SNVS_CAP)
/MPU_POWER/VDD_SOC_CAP: C36.1, C37.1, C38.1, C39.1, U1.G8 (VDD_SOC_CAP1), U1.H8 (VDD_SOC_CAP2), U1.J8 (VDD_SOC_CAP3), U1.J11 (VDD_SOC_CAP4), U1.K8 (VDD_SOC_CAP5), U1.K11 (VDD_SOC_CAP6), U1.L8 (VDD_SOC_CAP7), U1.L9 (VDD_SOC_CAP8), U1.L10 (VDD_SOC_CAP9), U1.L11 (VDD_SOC_CAP10)
GND: C29.2, C31.2, C32.2, C33.2, C34.2, C35.2, C36.2, C37.2, C38.2, C39.2, C40.2, C41.2, C42.2, C43.2, C44.2, C45.2, C46.2, U1.A1 (VSS1), U1.A17 (VSS2), U1.C3 (VSS3), U1.C7 (VSS4), U1.C11 (VSS5), U1.C15 (VSS6), U1.E8 (VSS7), U1.E11 (VSS8), U1.F6 (VSS9), U1.F7 (VSS10), U1.F8 (VSS11), U1.F9 (VSS12), U1.F10 (VSS13), U1.F11 (VSS14), U1.F12 (VSS15), U1.G3 (VSS16), U1.G5 (VSS17), U1.G7 (VSS18), U1.G12 (VSS19), U1.G15 (VSS20), U1.H7 (VSS21), U1.H12 (VSS22), U1.J5 (VSS23), U1.J7 (VSS24), U1.J12 (VSS25), U1.K7 (VSS26), U1.K12 (VSS27), U1.L3 (VSS28), U1.L7 (VSS29), U1.L12 (VSS30), U1.M7 (VSS31), U1.M8 (VSS32), U1.M9 (VSS33), U1.M10 (VSS34), U1.M11 (VSS35), U1.M12 (NGND_KEL0), U1.N3 (VSS36), U1.N5 (VSS37), U1.R3 (VSS38), U1.R5 (VSS39), U1.R7 (VSS40), U1.R11 (VSS41), U1.R16 (VSS42), U1.R17 (VSS43), U1.T14 (VSS44), U1.U1 (VSS45), U1.U14 (VSS46), U1.U17 (VSS47); also elsewhere on the board
VDD_HIGH_CAP: C45.1, C46.1, U1.R14 (VDD_HIGH_CAP1), U1.R15 (VDD_HIGH_CAP2); also elsewhere on the board

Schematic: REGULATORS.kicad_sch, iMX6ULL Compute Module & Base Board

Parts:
C71, C74, C76, C78, C80: 10uF; IPC-SMD-C-0805; Voltage 16V
C72, C77, C81: 220uF; ELKO-DIA-6.5mm-PS-2.54mm; Voltage 16V
C73: 100nF; IPC-SMD-C-0805; Voltage 50V
C75, C79: 100nF; IPC-SMD-C-0805; Voltage V
C82: 1uF; IPC-SMD-C-0402; Voltage 10V
D2: ES1D; IPC-DO-214AC(SMA)
L1, L3: 10uH; Inductor-SMD-FPI0403S-100M
P6: POWER IN; Connector-DG127-5.08-02P
R25, R27, R28: 10k; IPC-SMD-R-0402
R26: 33k2; IPC-SMD-R-0402
R29: 7k68; IPC-SMD-R-0402
U6: 78L05; TO92
U7, U8: TPS56x200; IPC-SOT-23-6

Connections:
+1V35: C80.1, C81.1, L3.1, R29.2; also elsewhere on the board
+3V3: C76.1, C77.1, L1.1, R26.2, R27.1; also elsewhere on the board
+5V: C74.1, U6.1 (VO); also elsewhere on the board
+12V: C71.1, C72.1, C73.1, C78.1, D2.2 (K), P6.1, U6.3 (VI), U7.3 (VIN), U7.5 (EN), U8.3 (VIN)
GND: C71.2, C72.2, C73.2, C74.2, C76.2, C77.2, C78.2, C80.2, C81.2, C82.2, D2.1 (A), P6.2, R25.1, R28.1, U6.2 (GND), U7.1 (GND), U8.1 (GND); also elsewhere on the board
unnamed: C75.1, U7.6 (VBST)
unnamed: C75.2, L1.2, U7.2 (SW)
unnamed: C79.1, U8.6 (VBST)
unnamed: C79.2, L3.2, U8.2 (SW)
unnamed: C82.1, R27.2, U8.5 (EN)
unnamed: R25.2, R26.1, U7.4 (VFB)
unnamed: R28.2, R29.1, U8.4 (VFB)
